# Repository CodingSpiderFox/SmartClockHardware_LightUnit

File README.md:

# SmartClockHardware (LightUnit)

This is part of the hardware specification for my smart clock project.

The hardware consists of one device for the wake-up light functionality and another for the controls and display

The lighting unit is controlled by the NodeMCU (1.1) via MQTT. Therefore, a MQTT broker is needed. It's likely that RabbitMQ will be chosen and run on a raspberry PI. This way, it will also be possible to integrate the SmartClock into your Smart Home setup using openHAB.

The lighting unit consists of two parts held in two encasings:

1.1) The controlling NodeMCU with a PIR sensor so you can configure the lighting unit to light up automatically on motion detection during daytime and automatically disable this function at night when you go to sleep.

1.2) WS2812B RGB LED strips, 5x 12V warm white LED panels to be able to have different lighting scenes.

The software can be found here:

Control unit: https://github.com/CodingSpiderFox/SmartClockControlUnit (not implemented yet)
Lighting unit: (not implemented yet)

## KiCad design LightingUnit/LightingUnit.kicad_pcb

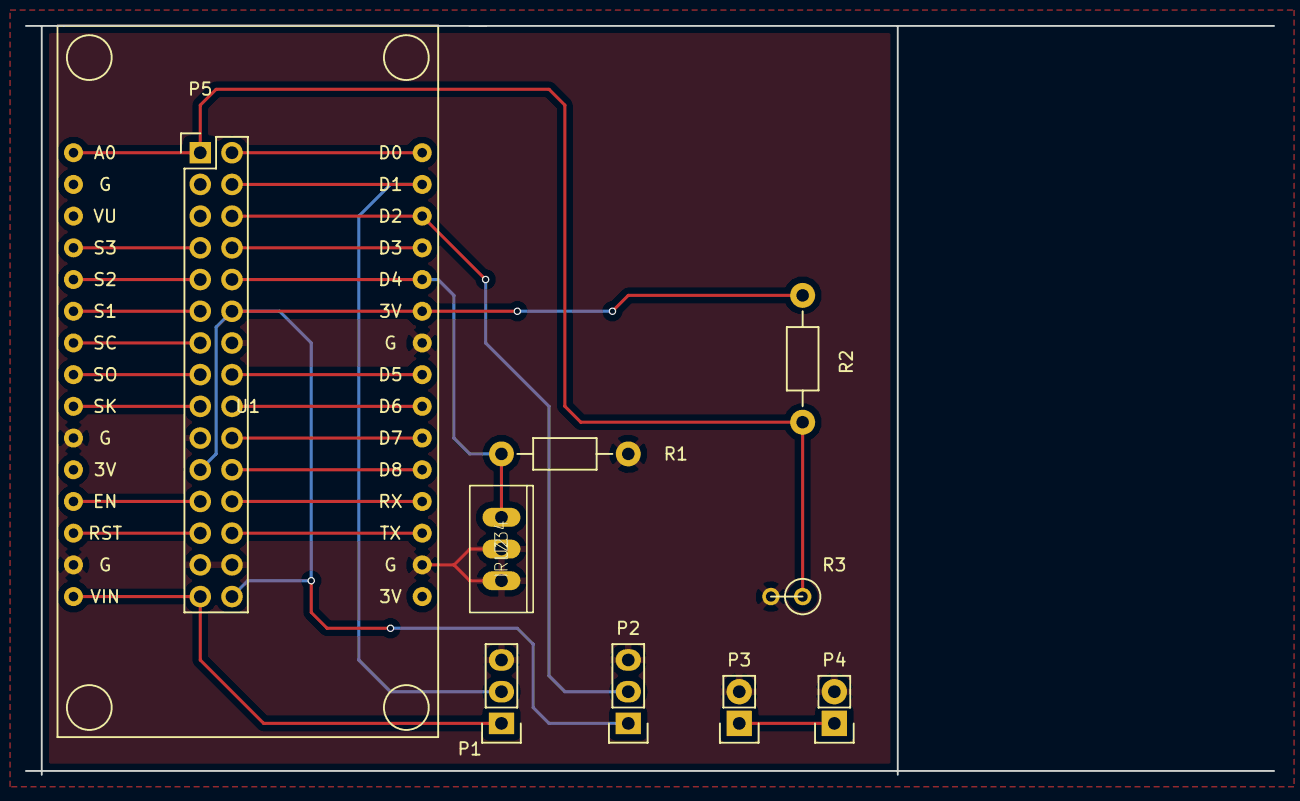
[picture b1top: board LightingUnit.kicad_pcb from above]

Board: 2 copper layers, 100.0 x 60.0 mm, 10 parts (0 on the bottom side), 24 nets.

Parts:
P1, P2: Pin_Header_Straight_1x03
P3, P4: Pin_Header_Straight_1x02
P5: Pin_Header_Straight_2x15
R1, R2: 10k; Resistor_Horizontal_RM10mm
R3: LDR; R1
U1: NodeMCU1.0(12-E)
U2: IRLZ34; TO-220(2)

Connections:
+3V3: P2.1, P5.12, P5.21, P5.30, R2.1, U1.25
+5V: P1.1, P5.29, U1.15
+12V: P3.1, P4.1
A0: P5.1, R2.2, R3.1, U1.1
CLK: P5.17, U1.9
CMD: P5.13, U1.7
D0: P5.2, U1.30
D1: P1.2, P5.4, U1.29
D2: P2.2, P5.6, U1.28
D3: P5.8, U1.27
D4: P5.10, R1.1, U1.26, U2.IN
D5: P5.16, U1.23
D6: P5.18, U1.22
D7: P5.20, U1.21
D8: P5.22, U1.20
EN: P5.23, U1.12
GND: P1.3, P2.3, P3.2, P4.2, P5.14, P5.19, P5.27, P5.28, R1.2, R3.2, U1.10, U1.14, U1.17, U1.24, U2.GND, U2.OUT
RST: P5.25, U1.13
RX: P5.24, U1.19
SD0: P5.15, U1.8
SD1: P5.11, U1.6
SD2: P5.9, U1.5
SD3: P5.7, U1.4
TX: P5.26, U1.18

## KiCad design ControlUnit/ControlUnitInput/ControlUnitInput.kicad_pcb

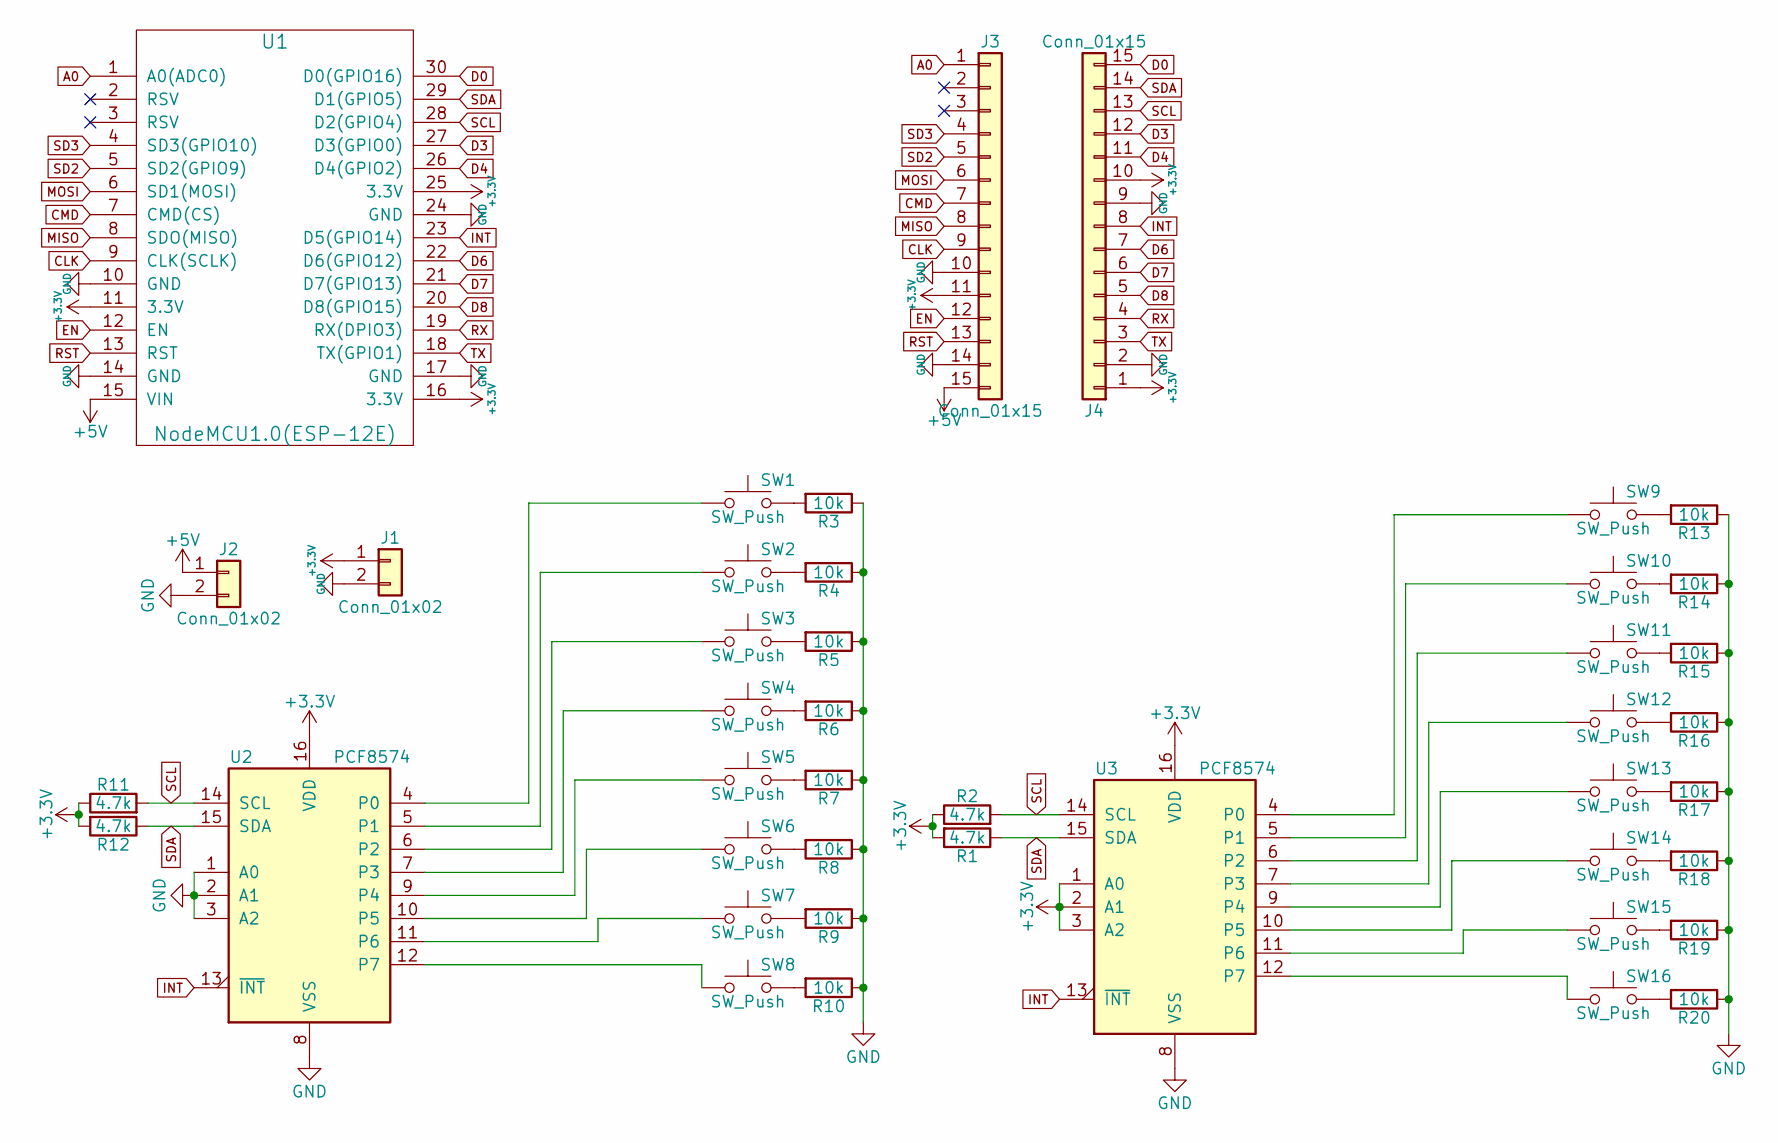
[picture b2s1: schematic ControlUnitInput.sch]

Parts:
J1, J2: Conn_01x02; Pin_Header_Straight_1x02_Pitch2.54mm
J3, J4: Conn_01x15; Pin_Header_Straight_1x15_Pitch2.54mm
R1, R2, R11, R12: 4.7k; R_Axial_DIN0204_L3.6mm_D1.6mm_P7.62mm_Horizontal
R3, R4, R5, R6, R7, R8, R9, R10, R13, R14, R15, R16, R17, R18, R19, R20: 10k; R_Axial_DIN0204_L3.6mm_D1.6mm_P7.62mm_Horizontal
SW1, SW2, SW3, SW4, SW5, SW6, SW7, SW8, SW9, SW10, SW11, SW12, SW13, SW14, SW15, SW16: SW_Push; SW_PUSH_6mm_h8mm
U1: NodeMCU1.0(ESP-12E); NodeMCU1.0(12-E)
U2, U3: PCF8574; DIP-16_W7.62mm

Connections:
+3V3: J1.1, J3.11, J4.1, J4.10, R1.2, R2.1, R11.1, R12.2, U1.11 (3.3V), U1.16 (3.3V), U1.25 (3.3V), U2.16 (VDD), U3.1 (A0), U3.2 (A1), U3.3 (A2), U3.16 (VDD)
+5V: J2.1, J3.15, U1.15 (VIN)
A0: J3.1, U1.1 (A0(ADC0))
CLK: J3.9, U1.9 (CLK(SCLK))
CMD: J3.7, U1.7 (CMD(CS))
D0: J4.15, U1.30 (D0(GPIO16))
D3: J4.12, U1.27 (D3(GPIO0))
D4: J4.11, U1.26 (D4(GPIO2))
D6: J4.7, U1.22 (D6(GPIO12))
D7: J4.6, U1.21 (D7(GPIO13))
D8: J4.5, U1.20 (D8(GPIO15))
EN: J3.12, U1.12 (EN)
GND: J1.2, J2.2, J3.10, J3.14, J4.2, J4.9, R3.1, R4.1, R5.1, R6.1, R7.1, R8.1, R9.1, R10.1, R13.1, R14.1, R15.1, R16.1, R17.1, R18.1, R19.1, R20.1, U1.10 (GND), U1.14 (GND), U1.17 (GND), U1.24 (GND), U2.1 (A0), U2.2 (A1), U2.3 (A2), U2.8 (VSS), U3.8 (VSS)
INT: J4.8, U1.23 (D5(GPIO14)), U2.13 (~INT~), U3.13 (~INT~)
MISO: J3.8, U1.8 (SDO(MISO))
MOSI: J3.6, U1.6 (SD1(MOSI))
unnamed: R3.2, SW1.2
unnamed: R4.2, SW2.2
unnamed: R5.2, SW3.2
unnamed: R6.2, SW4.2
unnamed: R7.2, SW5.2
unnamed: R8.2, SW6.2
unnamed: R9.2, SW7.2
unnamed: R10.2, SW8.2
unnamed: R13.2, SW9.2
unnamed: R14.2, SW10.2
unnamed: R15.2, SW11.2
unnamed: R16.2, SW12.2
unnamed: R17.2, SW13.2
unnamed: R18.2, SW14.2
unnamed: R19.2, SW15.2
unnamed: R20.2, SW16.2
unnamed: SW1.1, U2.4 (P0)
unnamed: SW2.1, U2.5 (P1)
unnamed: SW3.1, U2.6 (P2)
unnamed: SW4.1, U2.7 (P3)
unnamed: SW5.1, U2.9 (P4)
unnamed: SW6.1, U2.10 (P5)
unnamed: SW7.1, U2.11 (P6)
unnamed: SW8.1, U2.12 (P7)
unnamed: SW9.1, U3.4 (P0)
unnamed: SW10.1, U3.5 (P1)
unnamed: SW11.1, U3.6 (P2)
unnamed: SW12.1, U3.7 (P3)
unnamed: SW13.1, U3.9 (P4)
unnamed: SW14.1, U3.10 (P5)
unnamed: SW15.1, U3.11 (P6)
unnamed: SW16.1, U3.12 (P7)
RST: J3.13, U1.13 (RST)
RX: J4.4, U1.19 (RX(DPIO3))
SCL: J4.13, R2.2, R11.2, U1.28 (D2(GPIO4)), U2.14 (SCL), U3.14 (SCL)
SD2: J3.5, U1.5 (SD2(GPIO9))
SD3: J3.4, U1.4 (SD3(GPIO10))
SDA: J4.14, R1.1, R12.1, U1.29 (D1(GPIO5)), U2.15 (SDA), U3.15 (SDA)
TX: J4.3, U1.18 (TX(GPIO1))

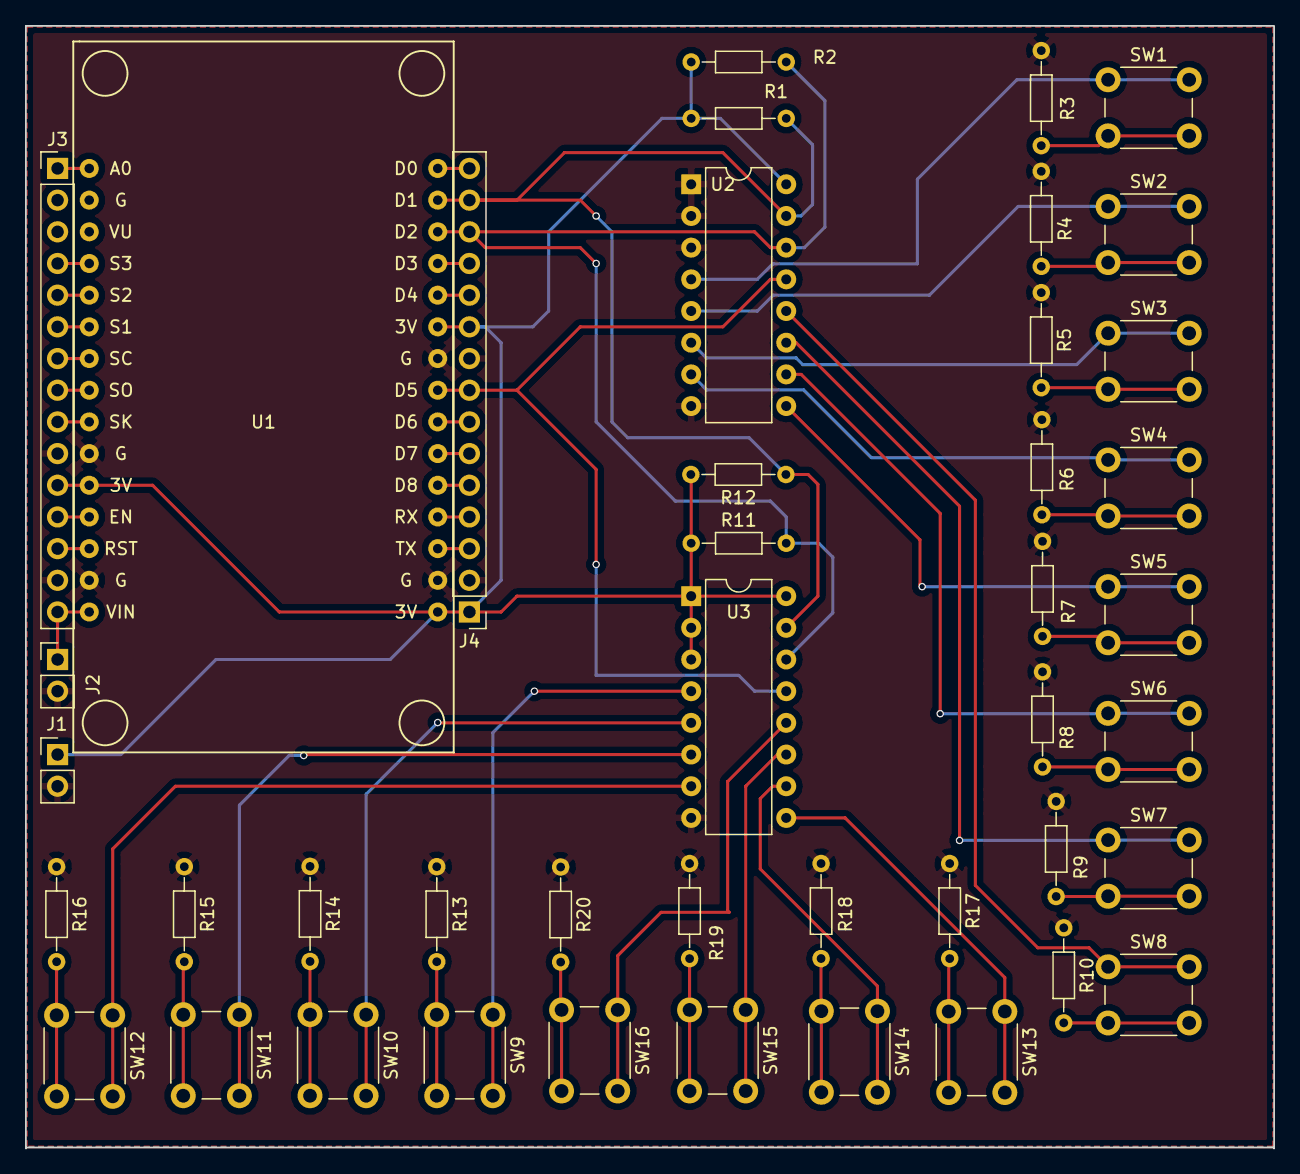
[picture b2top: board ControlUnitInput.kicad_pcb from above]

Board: 2 copper layers, 100.1 x 90.0 mm, 43 parts (0 on the bottom side), 55 nets.

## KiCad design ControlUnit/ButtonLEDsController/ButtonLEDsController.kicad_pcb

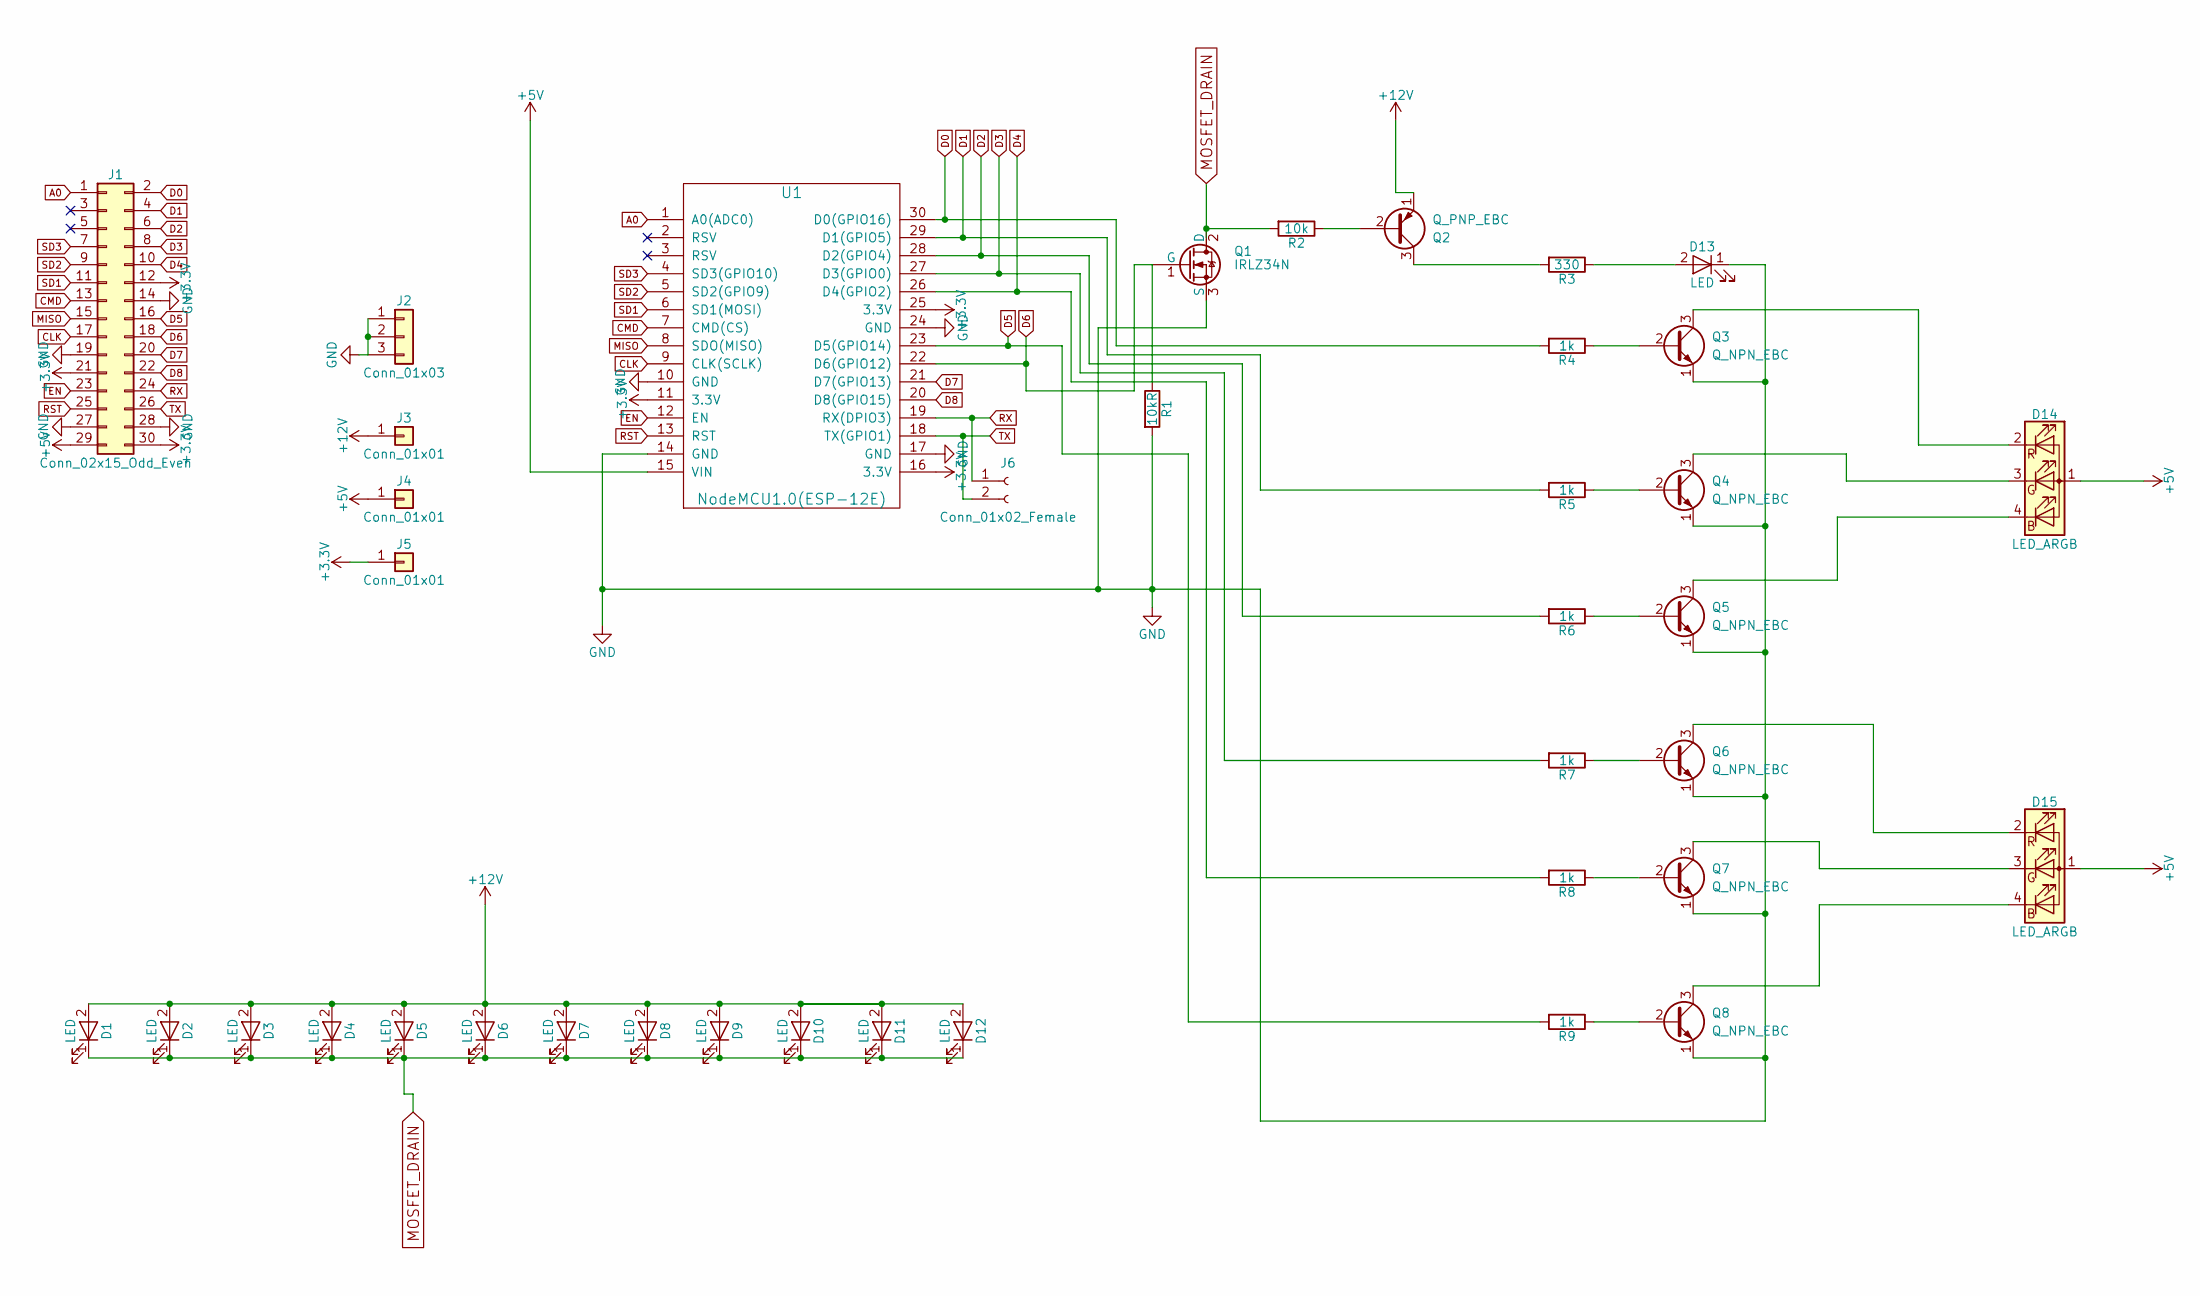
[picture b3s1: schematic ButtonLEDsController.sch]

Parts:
D1, D2, D3, D4, D5, D6, D7, D8, D9, D10, D11, D12, D13: LED; LED_D5.0mm
D14, D15: LED_ARGB; LED_D5.0mm-4
J1: Conn_02x15_Odd_Even; Pin_Header_Straight_2x15_Pitch2.54mm
J2: Conn_01x03; Pin_Header_Straight_1x03_Pitch2.54mm
J3, J4, J5: Conn_01x01; Pin_Header_Straight_1x01_Pitch2.54mm
J6: Conn_01x02_Female; Socket_Strip_Straight_1x02_Pitch2.54mm
Q1: IRLZ34N; TO-220
Q2: Q_PNP_EBC; TO-92_Molded_Narrow
Q3, Q4, Q5, Q6, Q7, Q8: Q_NPN_EBC; TO-92_Molded_Narrow
R1: 10kR; R_Axial_DIN0204_L3.6mm_D1.6mm_P7.62mm_Horizontal
R2: 10k; R_Axial_DIN0204_L3.6mm_D1.6mm_P7.62mm_Horizontal
R3: 330; R_Axial_DIN0204_L3.6mm_D1.6mm_P7.62mm_Horizontal
R4, R5, R6, R7, R8, R9: 1k; R_Axial_DIN0204_L3.6mm_D1.6mm_P7.62mm_Horizontal
U1: NodeMCU1.0(ESP-12E); NodeMCU1.0(12-E)

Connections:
+3V3: J1.12, J1.21, J1.30, J5.1, U1.11 (3.3V), U1.16 (3.3V), U1.25 (3.3V)
+5V: D14.1 (A), D15.1 (A), J1.29, J4.1, U1.15 (VIN)
+12V: D1.2 (A), D2.2 (A), D3.2 (A), D4.2 (A), D5.2 (A), D6.2 (A), D7.2 (A), D8.2 (A), D9.2 (A), D10.2 (A), D11.2 (A), D12.2 (A), J3.1, Q2.1 (E)
A0: J1.1, U1.1 (A0(ADC0))
CLK: J1.17, U1.9 (CLK(SCLK))
CMD: J1.13, U1.7 (CMD(CS))
D0: J1.2, R4.2, U1.30 (D0(GPIO16))
D1: J1.4, R5.2, U1.29 (D1(GPIO5))
D2: J1.6, R6.2, U1.28 (D2(GPIO4))
D3: J1.8, R7.2, U1.27 (D3(GPIO0))
D4: J1.10, R8.2, U1.26 (D4(GPIO2))
D5: J1.16, R9.2, U1.23 (D5(GPIO14))
D6: J1.18, Q1.1 (G), R1.1, U1.22 (D6(GPIO12))
D7: J1.20, U1.21 (D7(GPIO13))
D8: J1.22, U1.20 (D8(GPIO15))
EN: J1.23, U1.12 (EN)
GND: D13.1 (K), J1.14, J1.19, J1.27, J1.28, J2.1, J2.2, J2.3, Q1.3 (S), Q3.1 (E), Q4.1 (E), Q5.1 (E), Q6.1 (E), Q7.1 (E), Q8.1 (E), R1.2, U1.10 (GND), U1.14 (GND), U1.17 (GND), U1.24 (GND)
MISO: J1.15, U1.8 (SDO(MISO))
MOSFET_DRAIN: D1.1 (K), D2.1 (K), D3.1 (K), D4.1 (K), D5.1 (K), D6.1 (K), D7.1 (K), D8.1 (K), D9.1 (K), D10.1 (K), D11.1 (K), D12.1 (K), Q1.2 (D), R2.2
unnamed: D13.2 (A), R3.1
unnamed: D14.2 (RK), Q3.3 (C)
unnamed: D14.3 (GK), Q4.3 (C)
unnamed: D14.4 (BK), Q5.3 (C)
unnamed: D15.2 (RK), Q6.3 (C)
unnamed: D15.3 (GK), Q7.3 (C)
unnamed: D15.4 (BK), Q8.3 (C)
unnamed: Q2.2 (B), R2.1
unnamed: Q2.3 (C), R3.2
unnamed: Q3.2 (B), R4.1
unnamed: Q4.2 (B), R5.1
unnamed: Q5.2 (B), R6.1
unnamed: Q6.2 (B), R7.1
unnamed: Q7.2 (B), R8.1
unnamed: Q8.2 (B), R9.1
RST: J1.25, U1.13 (RST)
RX: J1.24, J6.1, U1.19 (RX(DPIO3))
SD1: J1.11, U1.6 (SD1(MOSI))
SD2: J1.9, U1.5 (SD2(GPIO9))
SD3: J1.7, U1.4 (SD3(GPIO10))
TX: J1.26, J6.2, U1.18 (TX(GPIO1))

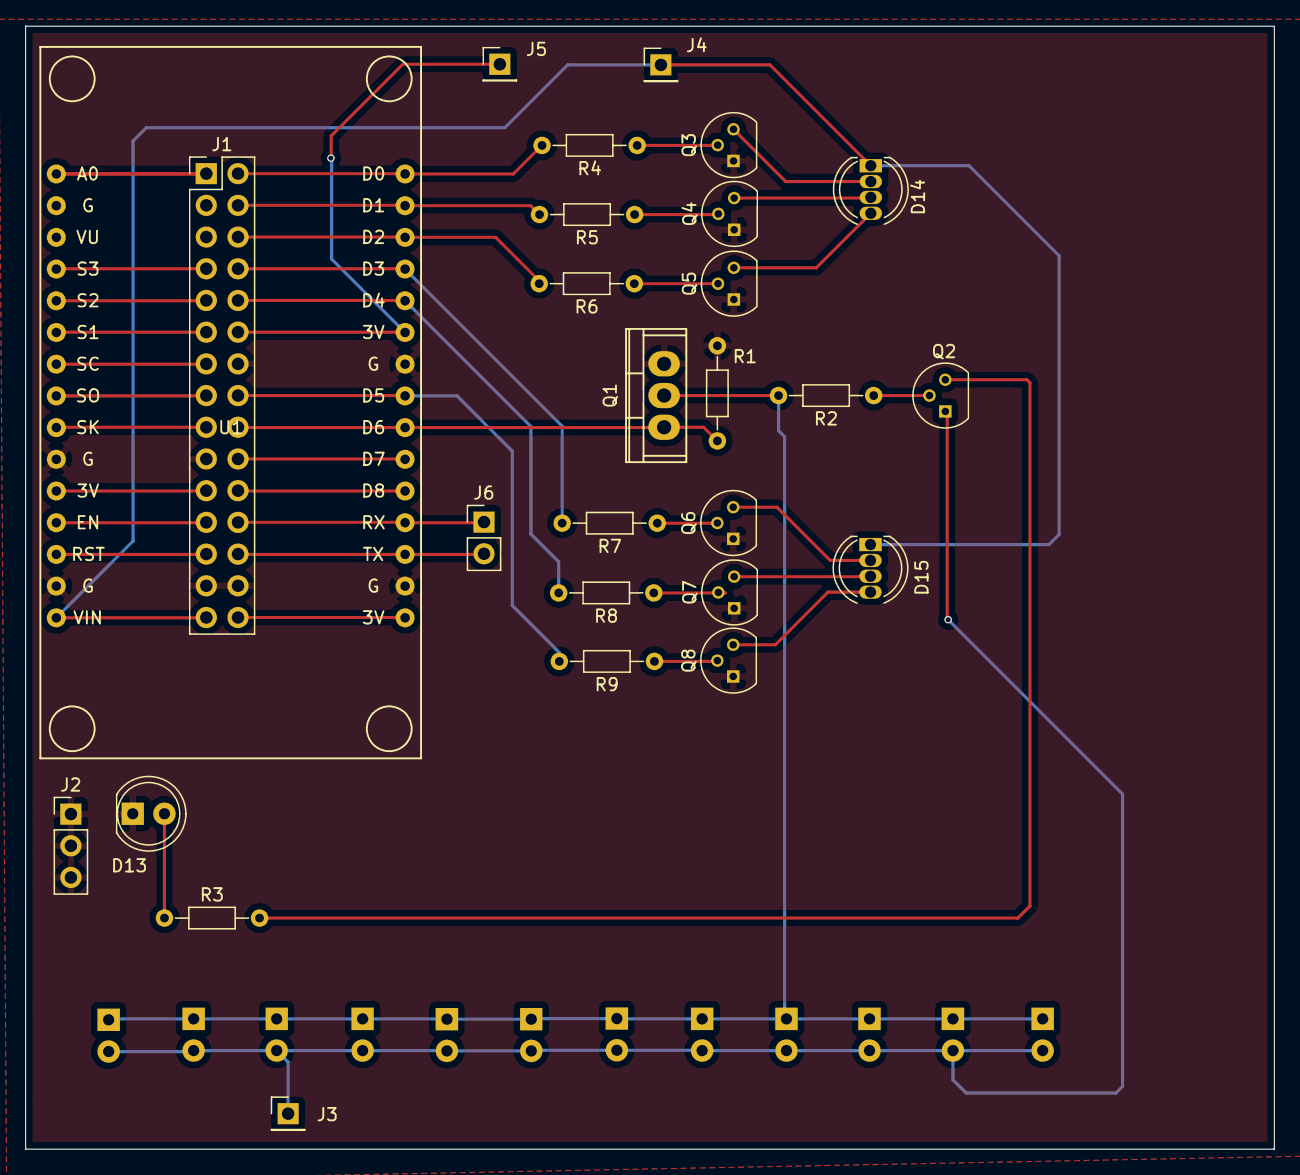
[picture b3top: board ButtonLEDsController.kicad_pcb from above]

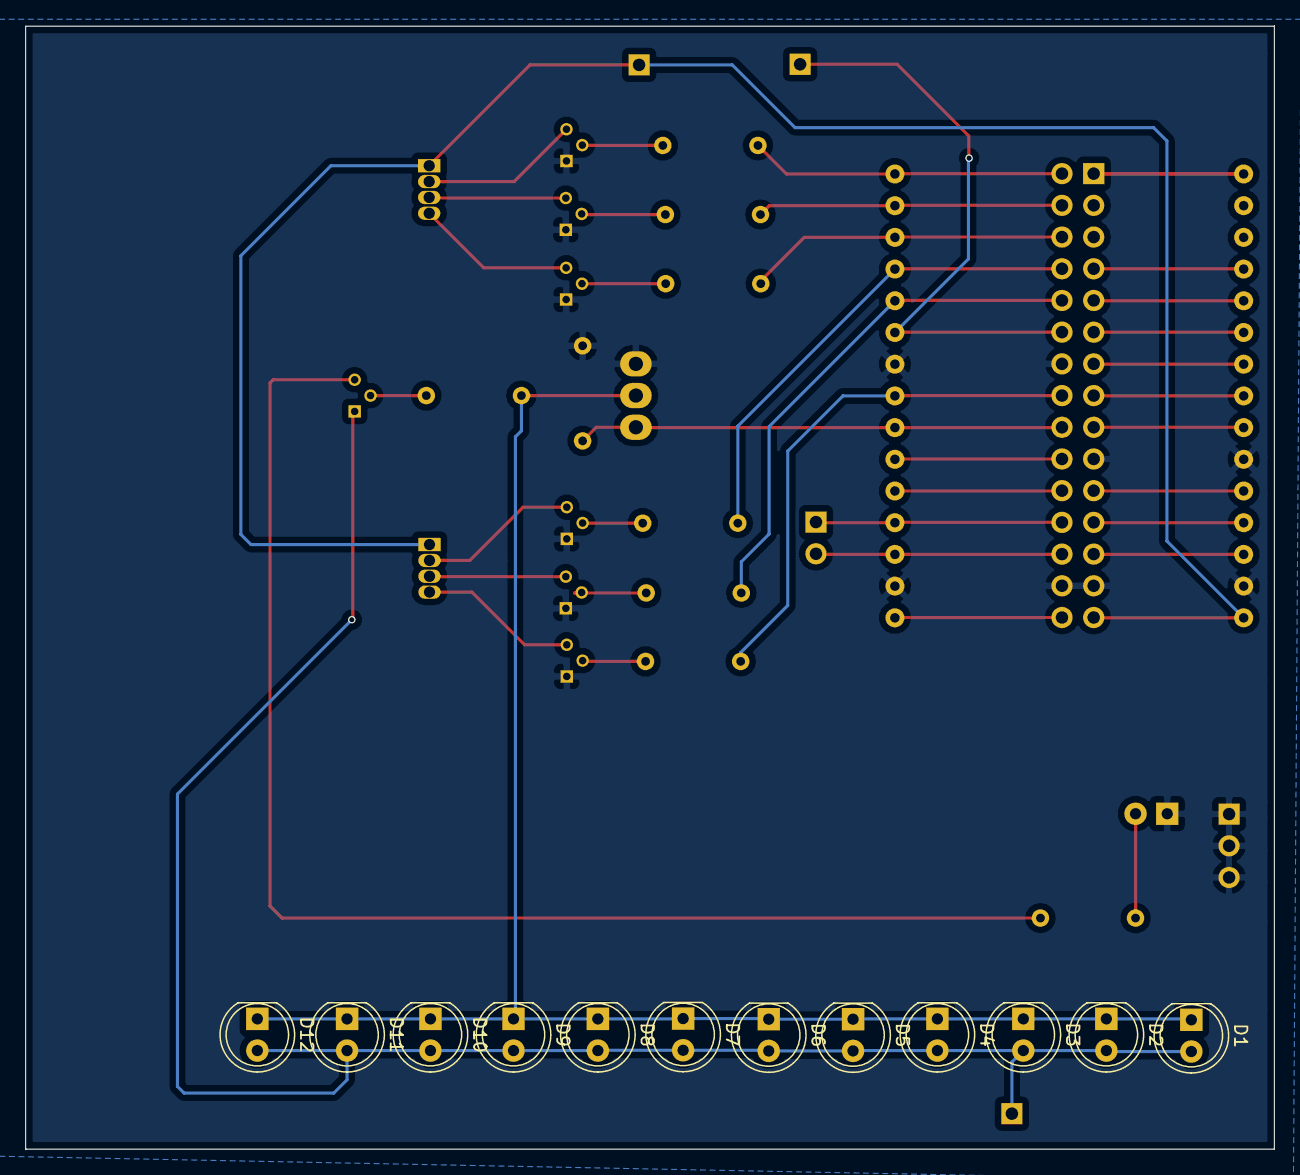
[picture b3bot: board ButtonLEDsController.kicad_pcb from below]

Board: 2 copper layers, 100.1 x 90.1 mm, 39 parts (12 on the bottom side), 40 nets.

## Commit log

2017-12-19 Create LICENSE
2017-12-23 restructure folder layout
2017-12-23 rename files
2017-12-23 fix library references
2017-12-23 add schematic for LEDs controller
2017-12-23 transistors in schematic taken from 3rd party lib were bad idea because default kicad footprints wouldn't match the pin references in the schematic (were E,B,C - needed to be 1,2,3 instead)
2017-12-23 clarify power connector voltages add license information and revisions to boards
2017-12-27 add lightunit schematic and pcb
2017-12-28 clean up, add license info
2017-12-28 add voltage labels
2018-01-01 add additional connectors for NodeMCU pins in order to be able to connect additional input devices later on
2018-01-04 realign components and fix track widths
2018-01-05 Revert "realign components and fix track widths"
    This reverts commit 8eef0b6b7679f1414a0b9c1d3560c4b6c89cb1c1.
2018-01-06 remove component which doesn't belong here
2018-01-06 Revert "remove component which doesn't belong here"
    This reverts commit 6766289d85d7250b5cbbadea44b7b0f64e1c22ee.
    Revert "Update README.md"
    This reverts commit 2de2f3ebc1b3d8aab12491cefdc5aa4339b4336a.
    Remote component "ControlUnit" which doesn't belong here

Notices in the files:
ControlUnit/ButtonLEDsController/ButtonLEDsController.kicad_pcb:
License: CERN OHL v1.2
